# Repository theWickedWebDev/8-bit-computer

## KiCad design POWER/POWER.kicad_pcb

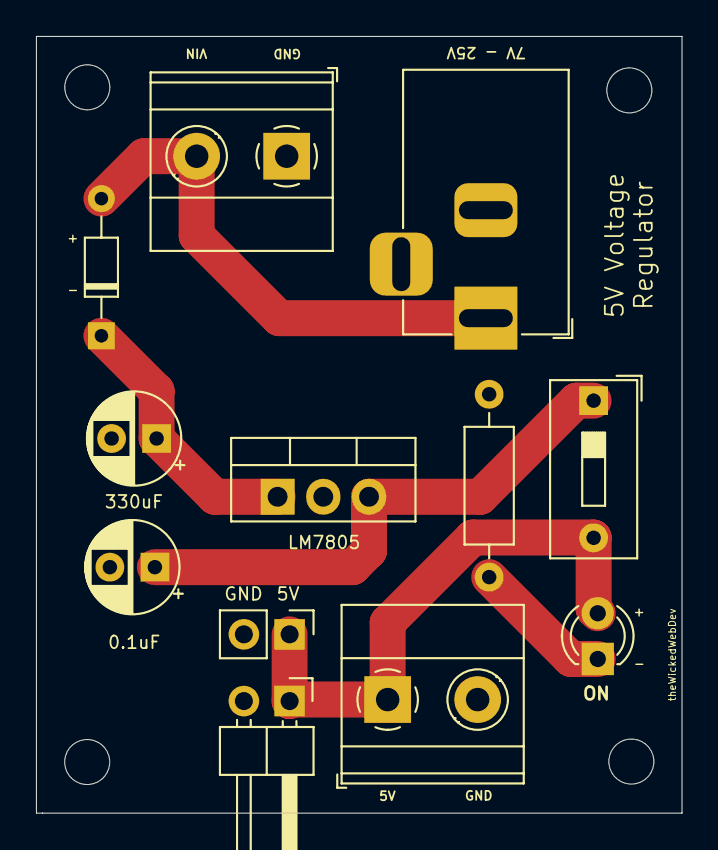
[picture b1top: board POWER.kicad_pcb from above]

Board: 2 copper layers, 35.9 x 43.1 mm, 12 parts (0 on the bottom side), 6 nets.

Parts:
C1, C2: CP1; CP_Radial_D5.0mm_P2.50mm
D1: D_Schottky; D_DO-34_SOD68_P7.62mm_Horizontal
D2: LED; LED_D3.0mm
J1, J4: Screw_Terminal_01x02; TerminalBlock_Phoenix_MKDS-1,5-2_1x02_P5.00mm_Horizontal
J2: Conn_01x02; PinHeader_1x02_P2.54mm_Horizontal
J3: Conn_01x02; PinHeader_1x02_P2.54mm_Vertical
J5: Barrel_Jack_MountingPin; BarrelJack_Horizontal
R1: R_Small_US; R_Axial_DIN0207_L6.3mm_D2.5mm_P10.16mm_Horizontal
SW1: SW_SPST; SW_DIP_SPSTx01_Slide_9.78x4.72mm_W7.62mm_P2.54mm
U1: LM7805_TO220; TO-220-3_Vertical

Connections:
GND: C1.2, C2.2, J1.1, J2.2, J3.2, J4.2, J5.2, R1.2, U1.2
unnamed: C1.1, D1.1, U1.1
unnamed: C2.1, SW1.1, U1.3
unnamed: D1.2, J1.2, J5.1
unnamed: D2.1, R1.1
VCC: D2.2, J2.1, J3.1, J4.1, SW1.2

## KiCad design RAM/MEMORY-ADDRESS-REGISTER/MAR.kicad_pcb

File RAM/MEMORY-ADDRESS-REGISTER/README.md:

# Memory Address Register

TODO: Description coming soon...

<br/>

## QA

<br/>

## PCB

<br/>

<br/>

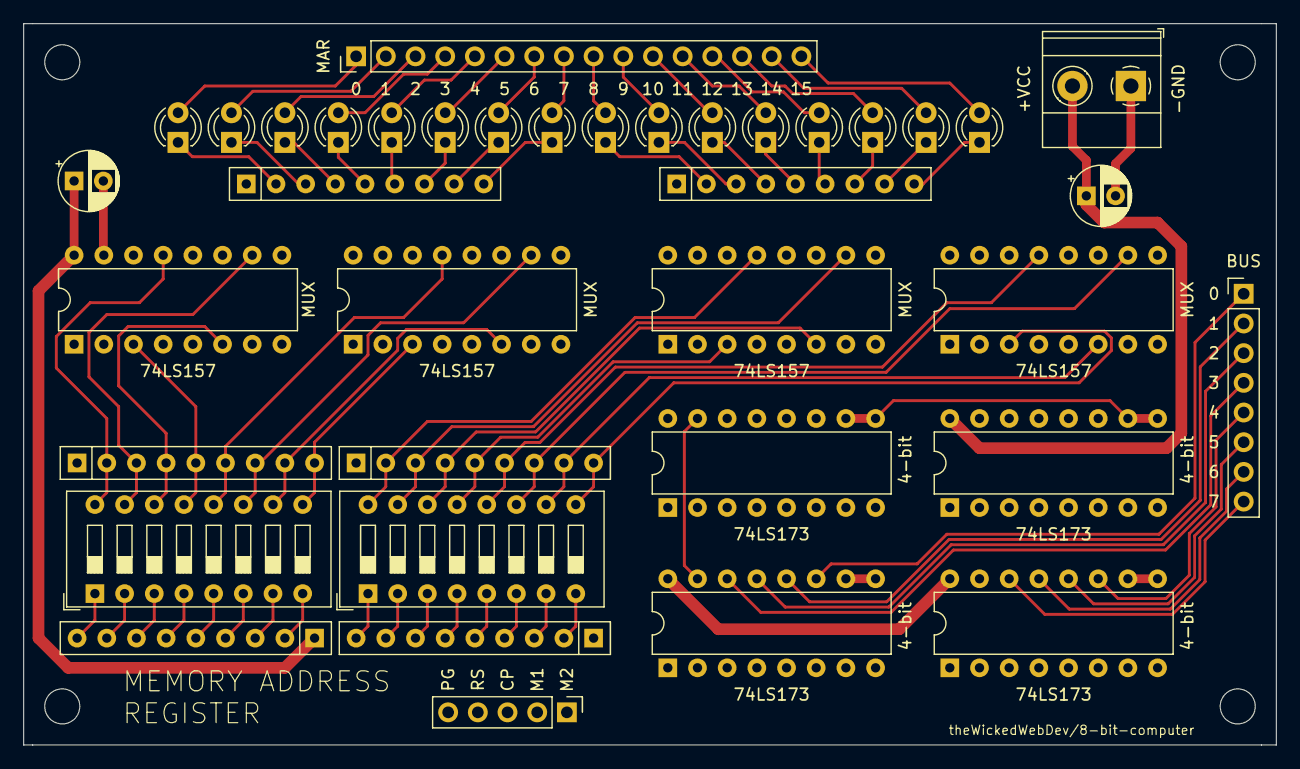
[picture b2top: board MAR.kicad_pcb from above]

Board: 4 copper layers, 107.2 x 61.7 mm, 38 parts (0 on the bottom side), 95 nets.

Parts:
C2, C3: CP1_Small; CP_Radial_D5.0mm_P2.50mm
D1, D2, D3, D4, D5, D6, D7, D8, D9, D10, D11, D12, D13, D14, D15, D16: LED; LED_D3.0mm
J1: Conn_01x08; PinHeader_1x16_P2.54mm_Vertical
J2: Conn_01x08; PinHeader_1x08_P2.54mm_Vertical
J3: Screw_Terminal_01x02; TerminalBlock_Phoenix_MKDS-1,5-2_1x02_P5.00mm_Horizontal
J4: Conn_01x05; PinHeader_1x05_P2.54mm_Vertical
RN1, RN2, RN4, RN5, RN6, RN7: R_Network08_US; R_Array_SIP9
SW1, SW2: SW_DIP_x08; SW_DIP_SPSTx08_Slide_9.78x22.5mm_W7.62mm_P2.54mm
U1, U4, U5, U8: 74LS157; DIP-16_W7.62mm
U2, U3, U6, U7: 74LS173; DIP-16_W7.62mm

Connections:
/CLOCK: J4.3, U2.7, U3.7, U6.7, U7.7
/MANUAL_MEM_ADR_00: RN6.2, SW2.16, U1.13
/MANUAL_MEM_ADR_01: RN6.3, SW2.15, U1.10
/MANUAL_MEM_ADR_02: RN6.4, SW2.14, U1.6
/MANUAL_MEM_ADR_03: RN6.5, SW2.13, U1.3
/MANUAL_MEM_ADR_04: RN6.6, SW2.12, U4.13
/MANUAL_MEM_ADR_05: RN6.7, SW2.11, U4.10
/MANUAL_MEM_ADR_06: RN6.8, SW2.10, U4.6
/MANUAL_MEM_ADR_07: RN6.9, SW2.9, U4.3
/MANUAL_MEM_ADR_08: RN4.2, SW1.16, U5.13
/MANUAL_MEM_ADR_09: RN4.3, SW1.15, U5.10
/MANUAL_MEM_ADR_10: RN4.4, SW1.14, U5.6
/MANUAL_MEM_ADR_11: RN4.5, SW1.13, U5.3
/MANUAL_MEM_ADR_12: RN4.6, SW1.12, U8.13
/MANUAL_MEM_ADR_13: RN4.7, SW1.11, U8.10
/MANUAL_MEM_ADR_14: RN4.8, SW1.10, U8.6
/MANUAL_MEM_ADR_15: RN4.9, SW1.9, U8.3
/MAR1_IN: J4.2, U6.9, U6.10, U7.9, U7.10
/MAR2_IN: J4.1, U2.9, U2.10, U3.9, U3.10
/MAR_00: U1.14, U7.3
/MAR_01: U1.11, U7.4
/MAR_02: U1.5, U7.5
/MAR_03: U1.2, U7.6
/MAR_04: U4.14, U6.3
/MAR_05: U4.11, U6.4
/MAR_06: U4.5, U6.5
/MAR_07: U4.2, U6.6
/MAR_08: U3.3, U5.14
/MAR_09: U3.4, U5.11
/MAR_10: U3.5, U5.5
/MAR_11: U3.6, U5.2
/MAR_12: U2.3, U8.14
/MAR_13: U2.4, U8.11
/MAR_14: U2.5, U8.5
/MAR_15: U2.6, U8.2
/MAR_RESET: J4.4, U2.15, U3.15, U6.15, U7.15
/MEM_ADR_00: D16.2, J1.1, U1.12
/MEM_ADR_01: D15.2, J1.2, U1.9
/MEM_ADR_02: D14.2, J1.3, U1.7
/MEM_ADR_03: D13.2, J1.4, U1.4
/MEM_ADR_04: D12.2, J1.5, U4.12
/MEM_ADR_05: D11.2, J1.6, U4.9
/MEM_ADR_06: D10.2, J1.7, U4.7
/MEM_ADR_07: D9.2, J1.8, U4.4
/MEM_ADR_08: D8.2, J1.9, U5.12
/MEM_ADR_09: D7.2, J1.10, U5.9
/MEM_ADR_10: D6.2, J1.11, U5.7
/MEM_ADR_11: D5.2, J1.12, U5.4
/MEM_ADR_12: D4.2, J1.13, U8.12
/MEM_ADR_13: D3.2, J1.14, U8.9
/MEM_ADR_14: D2.2, J1.15, U8.7
/MEM_ADR_15: D1.2, J1.16, U8.4
/PROGRAM_MODE: J4.5, U1.1, U4.1, U5.1, U8.1
GND: C2.2, C3.2, J3.1, RN1.1, RN2.1, RN4.1, RN6.1, U1.8, U1.15, U2.1, U2.2, U2.8, U3.1, U3.2, U3.8, U4.8, U4.15, U5.8, U5.15, U6.1, U6.2, U6.8, U7.1, U7.2, U7.8, U8.8, U8.15
unnamed: D1.1, RN1.9
unnamed: D2.1, RN1.8
unnamed: D3.1, RN1.7
unnamed: D4.1, RN1.6
unnamed: D5.1, RN1.5
unnamed: D6.1, RN1.4
unnamed: D7.1, RN1.3
unnamed: D8.1, RN1.2
unnamed: D9.1, RN2.9
unnamed: D10.1, RN2.8
unnamed: D11.1, RN2.7
unnamed: D12.1, RN2.6
unnamed: D13.1, RN2.5
unnamed: D14.1, RN2.4
unnamed: D15.1, RN2.3
unnamed: D16.1, RN2.2
unnamed: J2.1, U2.11, U6.11
unnamed: J2.2, U2.12, U6.12
unnamed: J2.3, U2.13, U6.13
unnamed: J2.4, U2.14, U6.14
unnamed: J2.5, U3.11, U7.11
unnamed: J2.6, U3.12, U7.12
unnamed: J2.7, U3.13, U7.13
unnamed: J2.8, U3.14, U7.14
unnamed: RN5.2, SW1.8
unnamed: RN5.3, SW1.7
unnamed: RN5.4, SW1.6
unnamed: RN5.5, SW1.5
unnamed: RN5.6, SW1.4
unnamed: RN5.7, SW1.3
unnamed: RN5.8, SW1.2
unnamed: RN5.9, SW1.1
unnamed: RN7.2, SW2.8
unnamed: RN7.3, SW2.7
unnamed: RN7.4, SW2.6
unnamed: RN7.5, SW2.5
unnamed: RN7.6, SW2.4
unnamed: RN7.7, SW2.3
unnamed: RN7.8, SW2.2
unnamed: RN7.9, SW2.1
VCC: C2.1, C3.1, J3.2, RN5.1, RN7.1, U1.16, U2.16, U3.16, U4.16, U5.16, U6.16, U7.16, U8.16

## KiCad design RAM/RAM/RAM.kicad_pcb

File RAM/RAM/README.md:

# RAM Modules

TODO: Description coming soon...

<br/>

## QA

<br/>

## PCB

<br/>

<br/>

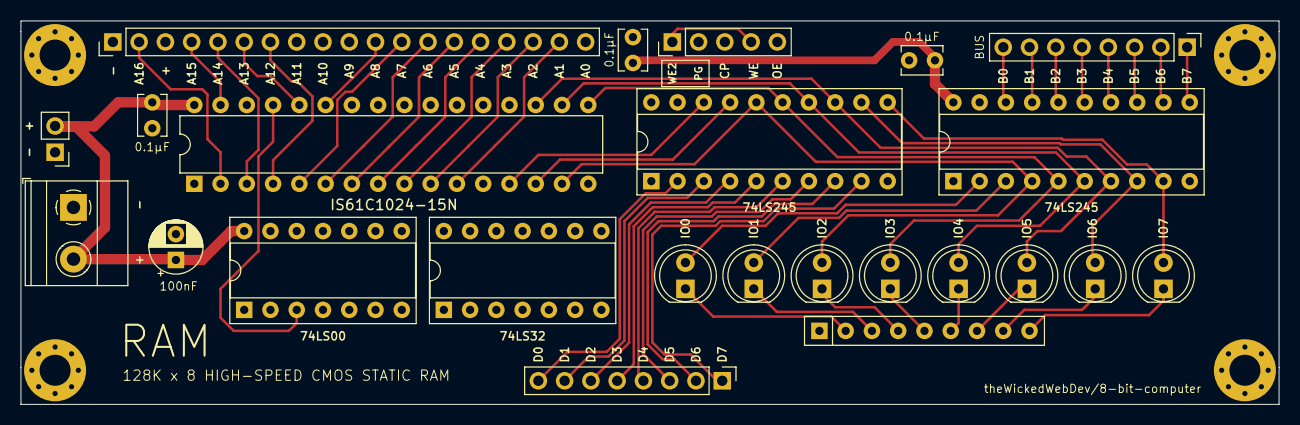
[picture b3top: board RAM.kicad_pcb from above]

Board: 4 copper layers, 121.7 x 37.1 mm, 24 parts (0 on the bottom side), 57 nets.

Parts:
C1: CP1_Small; CP_Radial_D5.0mm_P2.50mm
C2, C3, C4: C_Small; C_Disc_D3.8mm_W2.6mm_P2.50mm
D1, D2, D3, D4, D5, D6, D7, D8: LED; LED_D5.0mm
J1: Conn_01x19; PinHeader_1x19_P2.54mm_Vertical
J2: Conn_01x05; PinHeader_1x05_P2.54mm_Vertical
J3: Conn_01x02; PinHeader_1x02_P2.54mm_Vertical
J4: Screw_Terminal_01x02; TerminalBlock_Phoenix_MKDS-1,5-2_1x02_P5.00mm_Horizontal
J6, J7: Conn_01x08; PinHeader_1x08_P2.54mm_Vertical
RN1: R_Network08_US; R_Array_SIP9
U1: IS61C1024-15N; DIP-32_W7.62mm
U2, U3: 74LS245; DIP-20_W7.62mm_Socket
U4: 74LS00; DIP-14_W7.62mm_Socket
U6: 74LS32; DIP-14_W7.62mm_Socket

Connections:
/IO0: D8.2, U1.13, U2.2, U3.18
/IO1: D7.2, U1.14, U2.3, U3.17
/IO2: D6.2, U1.15, U2.4, U3.16
/IO3: D5.2, U1.17, U2.5, U3.15
/IO4: D4.2, U1.18, U2.6, U3.14
/IO5: D3.2, U1.19, U2.7, U3.13
/IO6: D2.2, U1.20, U2.8, U3.12
/IO7: D1.2, U1.21, U2.9, U3.11
A0: J1.19, U1.12
A1: J1.18, U1.11
A2: J1.17, U1.10
A3: J1.16, U1.9
A4: J1.15, U1.8
A5: J1.14, U1.7
A6: J1.13, U1.6
A7: J1.12, U1.5
A8: J1.11, U1.27
A9: J1.10, U1.26
A10: J1.9, U1.23
A11: J1.8, U1.25
A12: J1.7, U1.4
A13: J1.6, U1.28
A14: J1.5, U1.3
A15: J1.4, U1.31
A16: J1.2, U1.2
BUS0: J6.8, U2.18
BUS1: J6.7, U2.17
BUS2: J6.6, U2.16
BUS3: J6.5, U2.15
BUS4: J6.4, U2.14
BUS5: J6.3, U2.13
BUS6: J6.2, U2.12
BUS7: J6.1, U2.11
CLOCK: J2.3, U6.2
D0: J7.8, U3.2
D1: J7.7, U3.3
D2: J7.6, U3.4
D3: J7.5, U3.5
D4: J7.4, U3.6
D5: J7.3, U3.7
D6: J7.2, U3.8
D7: J7.1, U3.9
GND: C1.2, C2.2, C3.2, C4.2, J1.1, J3.1, J4.1, RN1.1, U1.16, U1.22, U1.24, U2.10, U3.10, U4.7, U6.7
unnamed: D1.1, RN1.9
unnamed: D2.1, RN1.8
unnamed: D3.1, RN1.7
unnamed: D4.1, RN1.6
unnamed: D5.1, RN1.5
unnamed: D6.1, RN1.4
unnamed: D7.1, RN1.3
unnamed: D8.1, RN1.2
unnamed: U1.29, U3.19, U4.3
unnamed: U4.1, U6.3
OUTPUT_ENABLE: J2.5, U2.19
PROGRAM_MODE: J2.2, U6.1
VCC: C1.1, C2.1, C3.1, C4.1, J1.3, J3.2, J4.2, U1.30, U1.32, U2.1, U2.20, U3.1, U3.20, U4.14, U6.14
WRITE_ENABLE: J2.1, J2.4, U4.2

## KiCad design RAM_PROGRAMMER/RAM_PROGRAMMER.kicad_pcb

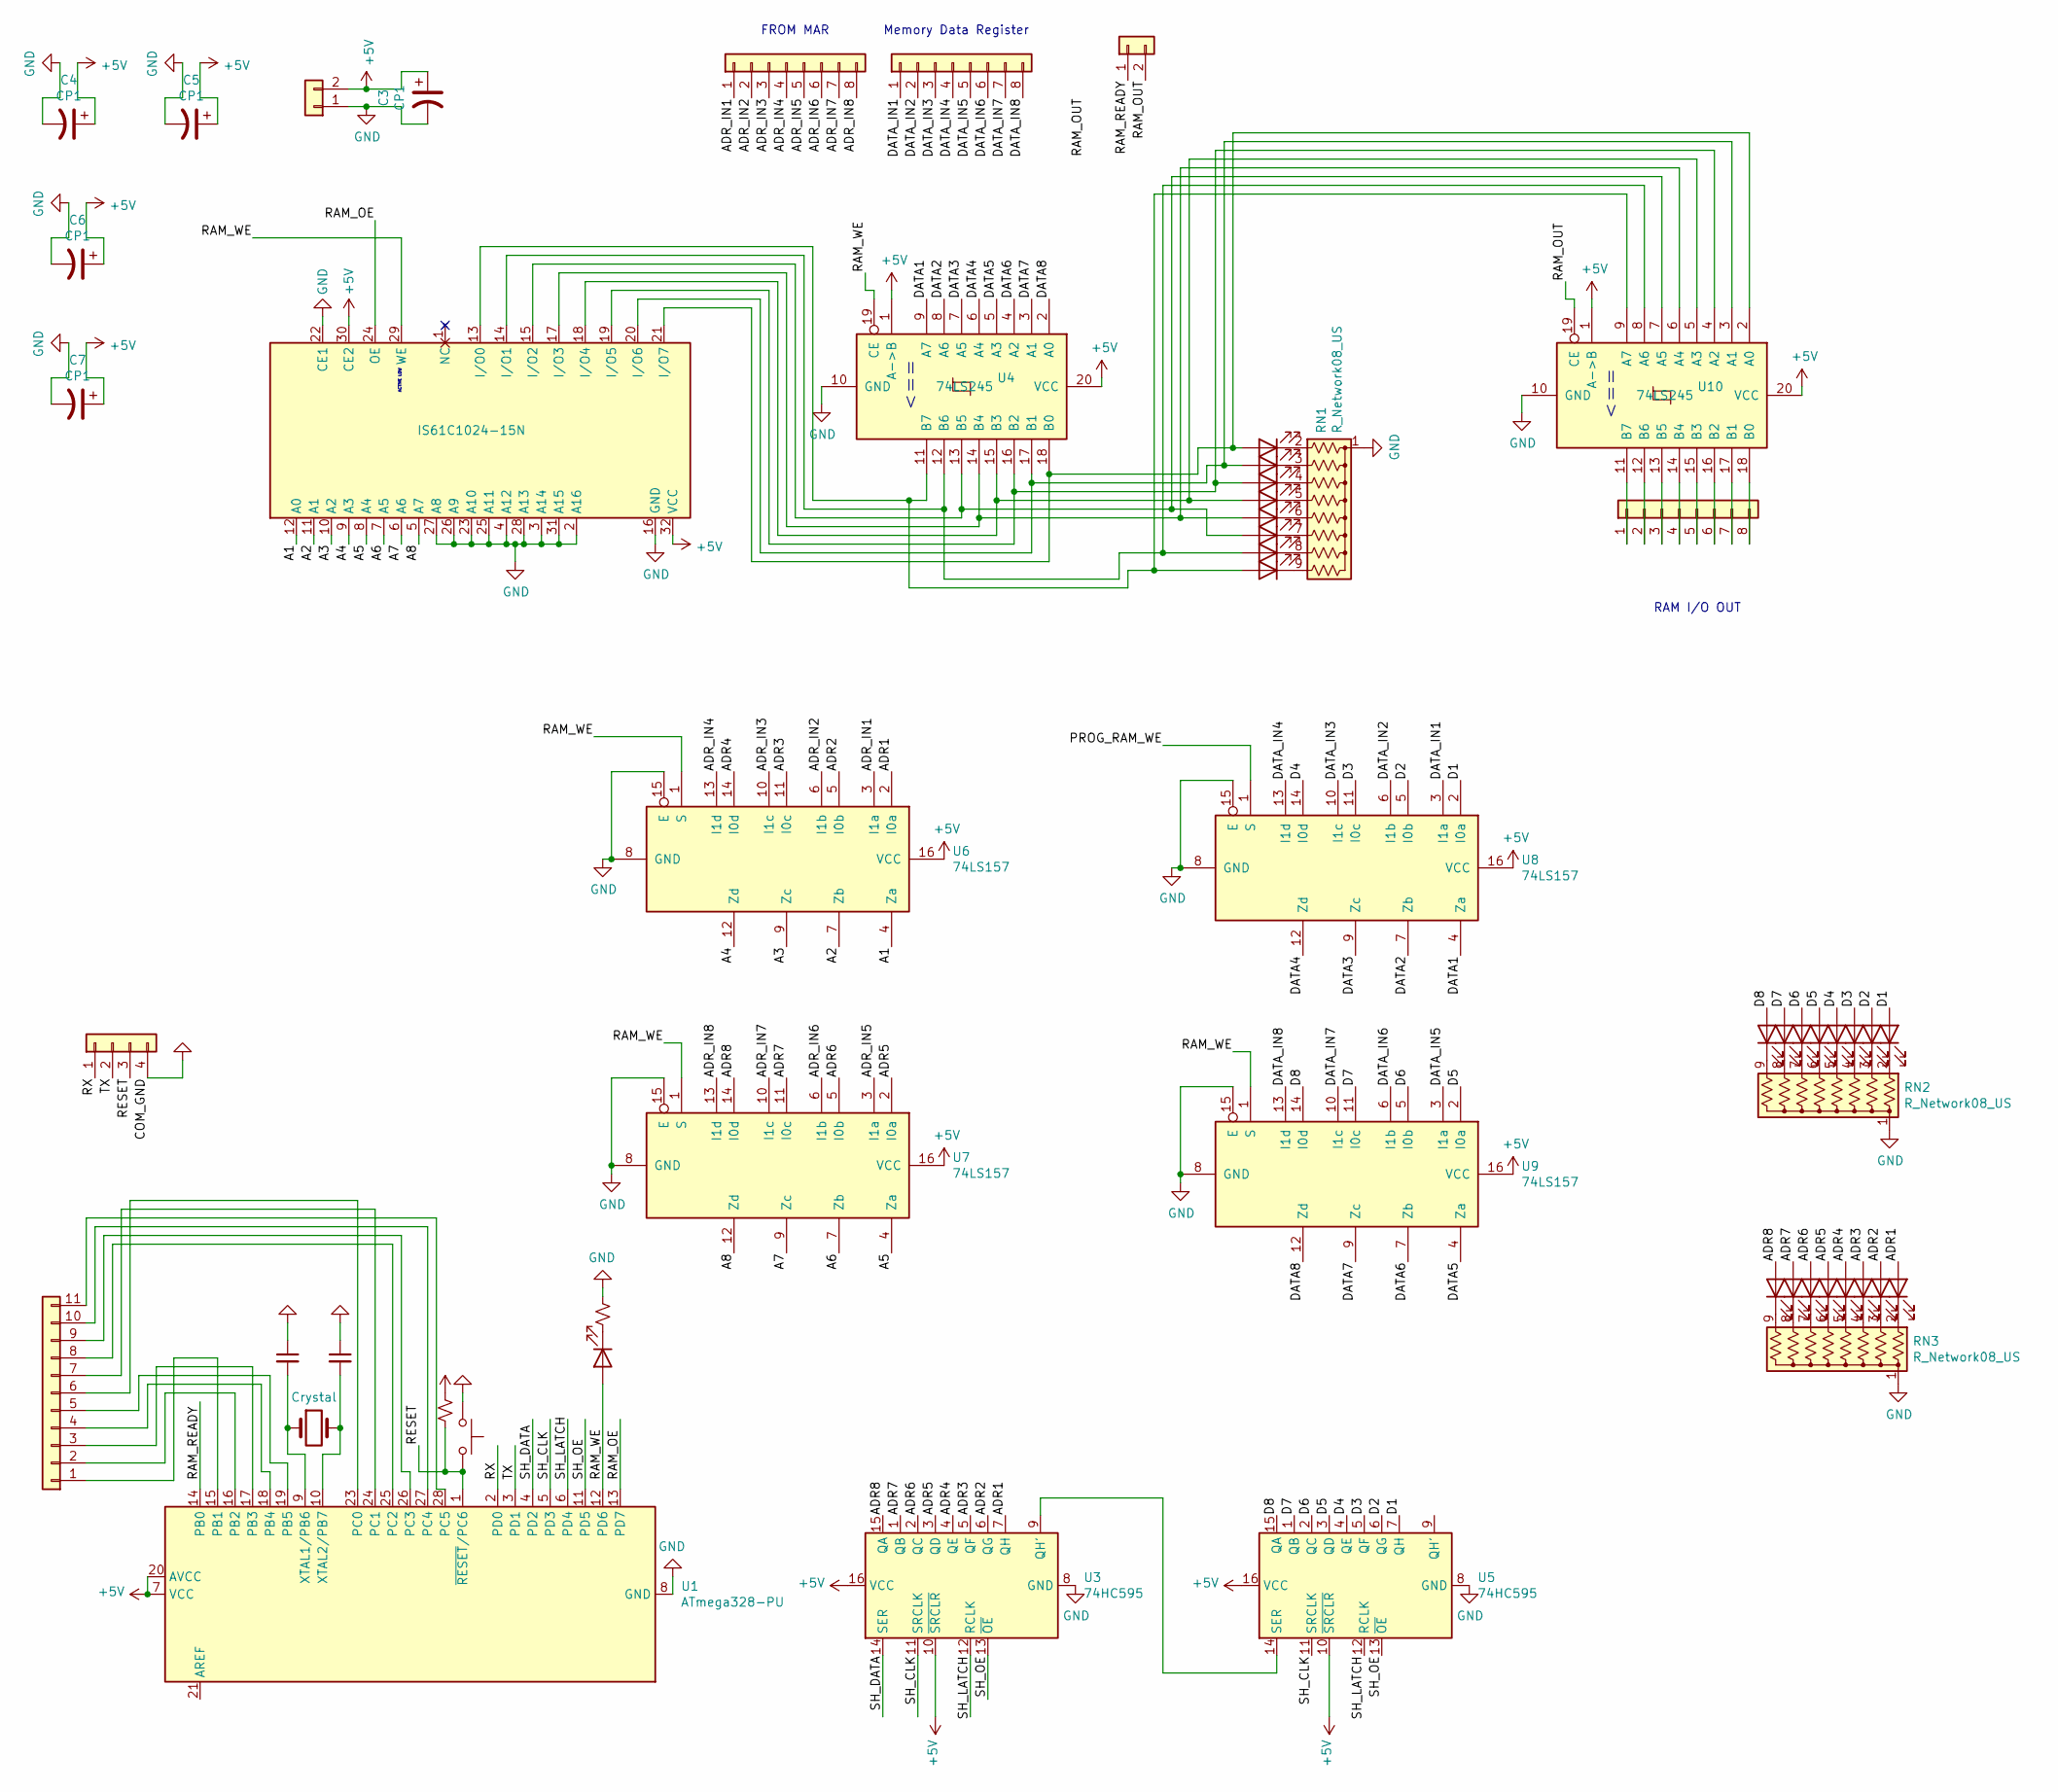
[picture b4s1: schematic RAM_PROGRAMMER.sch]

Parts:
C1, C2: C_Small; C_Disc_D3.8mm_W2.6mm_P2.50mm
C3, C4, C5, C6, C7: CP1; C_Radial_D4.0mm_H5.0mm_P1.50mm
D1, D2, D3, D4, D5, D6, D7, D8, D9, D10, D11, D12, D13, D14, D15, D16, D17, D18, D19, D20, D21, D22, D23, D24, D25: LED; LED_D3.0mm
J1, J5: Conn_01x02; PinHeader_1x02_P2.54mm_Vertical
J2, J3, J4: Conn_01x08; PinHeader_1x08_P2.54mm_Vertical
J6: Conn_01x04; PinHeader_1x04_P2.54mm_Vertical
J7: Conn_01x11; PinHeader_1x11_P2.54mm_Vertical
R1: R_Small_US; R_Axial_DIN0207_L6.3mm_D2.5mm_P7.62mm_Horizontal
R2: R_Small_US; R_Axial_DIN0204_L3.6mm_D1.6mm_P7.62mm_Horizontal
RN1, RN2, RN3: R_Network08_US; R_Array_SIP9
SW1: SW_Push; SW_PUSH_6mm
U1: ATmega328-PU; DIP-28_W7.62mm
U2: IS61C1024-15N; DIP-32_W7.62mm
U3, U5: 74HC595; DIP-16_W7.62mm
U4, U10: 74LS245; DIP-20_W7.62mm
U6, U7, U8, U9: 74LS157; DIP-16_W7.62mm
Y1: Crystal; Resonator-2Pin_W7.0mm_H2.5mm

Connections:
+5V: C3.1, C4.1, C5.1, C6.1, C7.1, J1.2, R1.1, U1.7 (VCC), U1.20 (AVCC), U2.30 (CE2), U2.32 (VCC), U3.10 (~SRCLR), U3.16 (VCC), U4.1 (A->B), U4.20 (VCC), U5.10 (~SRCLR), U5.16 (VCC), U6.16 (VCC), U7.16 (VCC), U8.16 (VCC), U9.16 (VCC), U10.1 (A->B), U10.20 (VCC)
/A1: U2.12 (A0), U6.4 (Za)
/A2: U2.11 (A1), U6.7 (Zb)
/A3: U2.10 (A2), U6.9 (Zc)
/A4: U2.9 (A3), U6.12 (Zd)
/A5: U2.8 (A4), U7.4 (Za)
/A6: U2.7 (A5), U7.7 (Zb)
/A7: U2.6 (A6), U7.9 (Zc)
/A8: U2.5 (A7), U7.12 (Zd)
/ADR1: D24.2 (A), U3.7 (QH), U6.2 (I0a)
/ADR2: D22.2 (A), U3.6 (QG), U6.5 (I0b)
/ADR3: D20.2 (A), U3.5 (QF), U6.11 (I0c)
/ADR4: D18.2 (A), U3.4 (QE), U6.14 (I0d)
/ADR5: D16.2 (A), U3.3 (QD), U7.2 (I0a)
/ADR6: D14.2 (A), U3.2 (QC), U7.5 (I0b)
/ADR7: D12.2 (A), U3.1 (QB), U7.11 (I0c)
/ADR8: D10.2 (A), U3.15 (QA), U7.14 (I0d)
/ADR_IN1: J2.1, U6.3 (I1a)
/ADR_IN2: J2.2, U6.6 (I1b)
/ADR_IN3: J2.3, U6.10 (I1c)
/ADR_IN4: J2.4, U6.13 (I1d)
/ADR_IN5: J2.5, U7.3 (I1a)
/ADR_IN6: J2.6, U7.6 (I1b)
/ADR_IN7: J2.7, U7.10 (I1c)
/ADR_IN8: J2.8, U7.13 (I1d)
/D1: D23.2 (A), U5.7 (QH), U8.2 (I0a)
/D2: D21.2 (A), U5.6 (QG), U8.5 (I0b)
/D3: D19.2 (A), U5.5 (QF), U8.11 (I0c)
/D4: D17.2 (A), U5.4 (QE), U8.14 (I0d)
/D5: D15.2 (A), U5.3 (QD), U9.2 (I0a)
/D6: D13.2 (A), U5.2 (QC), U9.5 (I0b)
/D7: D11.2 (A), U5.1 (QB), U9.11 (I0c)
/D8: D9.2 (A), U5.15 (QA), U9.14 (I0d)
/DATA1: U4.9 (A7), U8.4 (Za)
/DATA2: U4.8 (A6), U8.7 (Zb)
/DATA3: U4.7 (A5), U8.9 (Zc)
/DATA4: U4.6 (A4), U8.12 (Zd)
/DATA5: U4.5 (A3), U9.4 (Za)
/DATA6: U4.4 (A2), U9.7 (Zb)
/DATA7: U4.3 (A1), U9.9 (Zc)
/DATA8: U4.2 (A0), U9.12 (Zd)
/DATA_IN1: J3.1, U8.3 (I1a)
/DATA_IN2: J3.2, U8.6 (I1b)
/DATA_IN3: J3.3, U8.10 (I1c)
/DATA_IN4: J3.4, U8.13 (I1d)
/DATA_IN5: J3.5, U9.3 (I1a)
/DATA_IN6: J3.6, U9.6 (I1b)
/DATA_IN7: J3.7, U9.10 (I1c)
/DATA_IN8: J3.8, U9.13 (I1d)
/PROG_RAM_WE: U8.1 (S)
/RAM_OE: U1.13 (PD7), U2.24 (OE)
/RAM_OUT: J5.2, U10.19 (CE)
/RAM_READY: J5.1, U1.14 (PB0)
/RAM_WE: D25.2 (A), U1.12 (PD6), U2.29 (WE), U4.19 (CE), U6.1 (S), U7.1 (S), U9.1 (S)
/RESET: J6.3, R1.2, SW1.2, U1.1 (~RESET~/PC6)
/RX: J6.1, U1.2 (PD0)
/SH_CLK: U1.5 (PD3), U3.11 (SRCLK), U5.11 (SRCLK)
/SH_DATA: U1.4 (PD2), U3.14 (SER)
/SH_LATCH: U1.6 (PD4), U3.12 (RCLK), U5.12 (RCLK)
/SH_OE: U1.11 (PD5), U3.13 (~OE), U5.13 (~OE)
/TX: J6.2, U1.3 (PD1)
GND: C1.1, C2.1, C3.2, C4.2, C5.2, C6.2, C7.2, J1.1, J6.4, R2.2, RN1.1 (common), RN2.1 (common), RN3.1 (common), SW1.1, U1.8 (GND), U1.22 (GND), U2.2 (A16), U2.3 (A14), U2.4 (A12), U2.16 (GND), U2.22 (CE1), U2.23 (A10), U2.25 (A11), U2.26 (A9), U2.27 (A8), U2.28 (A13), U2.31 (A15), U3.8 (GND), U4.10 (GND), U5.8 (GND), U6.8 (GND), U6.15 (E), U7.8 (GND), U7.15 (E), U8.8 (GND), U8.15 (E), U9.8 (GND), U9.15 (E), U10.10 (GND)
unnamed: C1.2, U1.9 (XTAL1/PB6), Y1.1
unnamed: C2.2, U1.10 (XTAL2/PB7), Y1.2
unnamed: D1.1 (K), RN1.2 (R1)
unnamed: D1.2 (A), U2.21 (I/O7), U4.18 (B0), U10.2 (A0)
unnamed: D2.1 (K), RN1.3 (R2)
unnamed: D2.2 (A), U2.20 (I/O6), U4.17 (B1), U10.3 (A1)
unnamed: D3.1 (K), RN1.4 (R3)
unnamed: D3.2 (A), U2.19 (I/O5), U4.16 (B2), U10.4 (A2)
unnamed: D4.1 (K), RN1.5 (R4)
unnamed: D4.2 (A), U2.18 (I/O4), U4.15 (B3), U10.5 (A3)
unnamed: D5.1 (K), RN1.6 (R5)
unnamed: D5.2 (A), U2.17 (I/O3), U4.14 (B4), U10.6 (A4)
unnamed: D6.1 (K), RN1.7 (R6)
unnamed: D6.2 (A), U2.15 (I/O2), U4.13 (B5), U10.7 (A5)
unnamed: D7.1 (K), RN1.8 (R7)
unnamed: D7.2 (A), U2.14 (I/O1), U4.12 (B6), U10.8 (A6)
unnamed: D8.1 (K), RN1.9 (R8)
unnamed: D8.2 (A), U2.13 (I/O0), U4.11 (B7), U10.9 (A7)
unnamed: D9.1 (K), RN2.9 (R8)
unnamed: D10.1 (K), RN3.9 (R8)
unnamed: D11.1 (K), RN2.8 (R7)
unnamed: D12.1 (K), RN3.8 (R7)
unnamed: D13.1 (K), RN2.7 (R6)
unnamed: D14.1 (K), RN3.7 (R6)
unnamed: D15.1 (K), RN2.6 (R5)
unnamed: D16.1 (K), RN3.6 (R5)
unnamed: D17.1 (K), RN2.5 (R4)
unnamed: D18.1 (K), RN3.5 (R4)
unnamed: D19.1 (K), RN2.4 (R3)
unnamed: D20.1 (K), RN3.4 (R3)
unnamed: D21.1 (K), RN2.3 (R2)
unnamed: D22.1 (K), RN3.3 (R2)
unnamed: D23.1 (K), RN2.2 (R1)
unnamed: D24.1 (K), RN3.2 (R1)
unnamed: D25.1 (K), R2.1
unnamed: J4.1, U10.11 (B7)
unnamed: J4.2, U10.12 (B6)
unnamed: J4.3, U10.13 (B5)
unnamed: J4.4, U10.14 (B4)
unnamed: J4.5, U10.15 (B3)
unnamed: J4.6, U10.16 (B2)
unnamed: J4.7, U10.17 (B1)
unnamed: J4.8, U10.18 (B0)
unnamed: J7.1, U1.15 (PB1)
unnamed: J7.2, U1.16 (PB2)
unnamed: J7.3, U1.17 (PB3)
unnamed: J7.4, U1.18 (PB4)
unnamed: J7.5, U1.19 (PB5)
unnamed: J7.6, U1.23 (PC0)
unnamed: J7.7, U1.24 (PC1)
unnamed: J7.8, U1.25 (PC2)
unnamed: J7.9, U1.26 (PC3)
unnamed: J7.10, U1.27 (PC4)
unnamed: J7.11, U1.28 (PC5)
unnamed: U3.9 (QH'), U5.14 (SER)

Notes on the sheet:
<==
ACTIVE LOW
FROM MAR
Memory Data Register
RAM I/O OUT

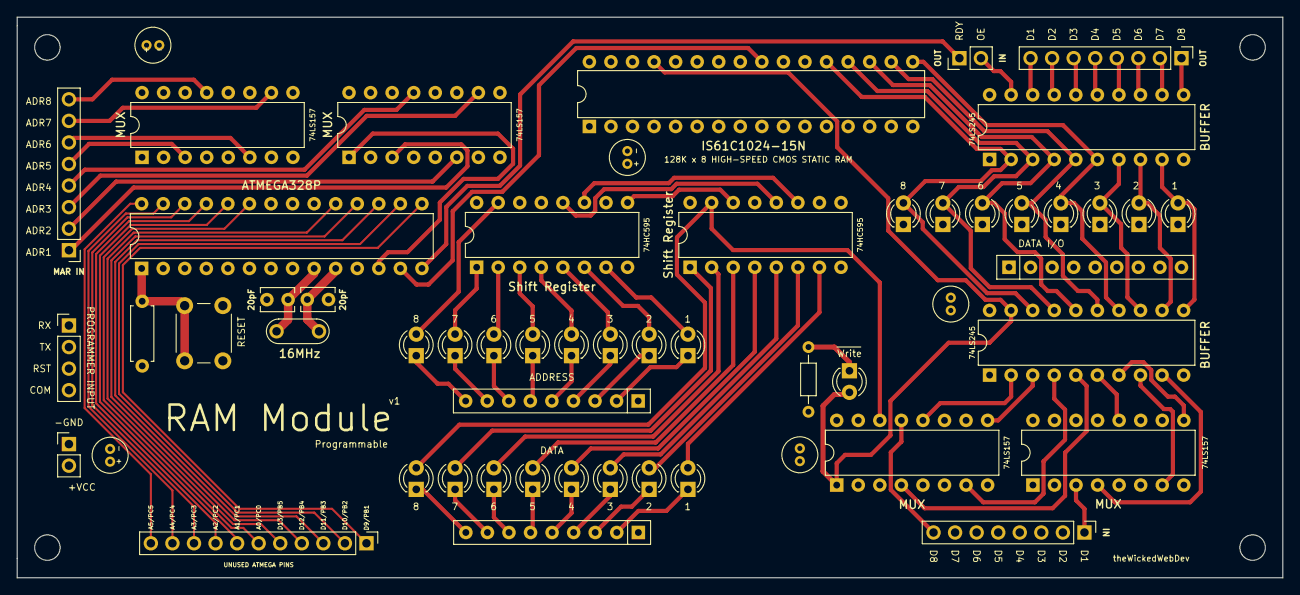
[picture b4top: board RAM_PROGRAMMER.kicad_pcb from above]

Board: 4 copper layers, 149.1 x 66.0 mm, 56 parts (0 on the bottom side), 116 nets.

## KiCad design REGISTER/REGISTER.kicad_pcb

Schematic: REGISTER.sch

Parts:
C1, C2, C3, C4: CP1; C_Radial_D5.0mm_H7.0mm_P2.00mm
D1, D2, D3, D4, D5, D6, D7, D8, D9, D10, D11, D12, D13, D14, D15, D16: LED; LED_D5.0mm
J1, J2, J5, J7, J8: Conn_01x08; PinHeader_1x08_P2.54mm_Vertical
J3: Conn_01x02; PinHeader_1x02_P2.54mm_Vertical
J6: Conn_01x07; PinHeader_1x07_P2.54mm_Vertical
RN1, RN2: R_Network08; R_Array_SIP9
U1, U4: 74LS245; DIP-20_W7.62mm
U2, U3, U5, U6: 74LS173; DIP-16_W7.62mm

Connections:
/A1: D8.2 (A), J7.1, J8.1, U1.9 (A7), U3.6 (Q3)
/A2: D7.2 (A), J7.2, J8.2, U1.8 (A6), U3.5 (Q2)
/A3: D6.2 (A), J7.3, J8.3, U1.7 (A5), U3.4 (Q1)
/A4: D5.2 (A), J7.4, J8.4, U1.6 (A4), U3.3 (Q0)
/A5: D4.2 (A), J7.5, J8.5, U1.5 (A3), U2.6 (Q3)
/A6: D3.2 (A), J7.6, J8.6, U1.4 (A2), U2.5 (Q2)
/A7: D2.2 (A), J7.7, J8.7, U1.3 (A1), U2.4 (Q1)
/A8: D1.2 (A), J7.8, J8.8, U1.2 (A0), U2.3 (Q0)
/AI: J6.5, U2.9 (E1), U2.10 (E2), U3.9 (E1), U3.10 (E2)
/AO: J6.4, U1.19 (CE)
/B1: D16.2 (A), J1.1, J2.1, U4.9 (A7), U6.6 (Q3)
/B2: D15.2 (A), J1.2, J2.2, U4.8 (A6), U6.5 (Q2)
/B3: D14.2 (A), J1.3, J2.3, U4.7 (A5), U6.4 (Q1)
/B4: D13.2 (A), J1.4, J2.4, U4.6 (A4), U6.3 (Q0)
/B5: D12.2 (A), J1.5, J2.5, U4.5 (A3), U5.6 (Q3)
/B6: D11.2 (A), J1.6, J2.6, U4.4 (A2), U5.5 (Q2)
/B7: D10.2 (A), J1.7, J2.7, U4.3 (A1), U5.4 (Q1)
/B8: D9.2 (A), J1.8, J2.8, U4.2 (A0), U5.3 (Q0)
/BI: J6.2, U5.9 (E1), U5.10 (E2), U6.9 (E1), U6.10 (E2)
/BO: J6.1, U4.19 (CE)
/CLK: J6.7, U2.7 (Cp), U3.7 (Cp), U5.7 (Cp), U6.7 (Cp)
/I1: J5.8, U1.11 (B7), U3.11 (D3), U4.11 (B7), U6.11 (D3)
/I2: J5.7, U1.12 (B6), U3.12 (D2), U4.12 (B6), U6.12 (D2)
/I3: J5.6, U1.13 (B5), U3.13 (D1), U4.13 (B5), U6.13 (D1)
/I4: J5.5, U1.14 (B4), U3.14 (D0), U4.14 (B4), U6.14 (D0)
/I5: J5.4, U1.15 (B3), U2.11 (D3), U4.15 (B3), U5.11 (D3)
/I6: J5.3, U1.16 (B2), U2.12 (D2), U4.16 (B2), U5.12 (D2)
/I7: J5.2, U1.17 (B1), U2.13 (D1), U4.17 (B1), U5.13 (D1)
/I8: J5.1, U1.18 (B0), U2.14 (D0), U4.18 (B0), U5.14 (D0)
GND: C1.2, C2.2, C3.2, C4.2, J3.2, RN1.1, RN2.1, U1.10 (GND), U2.1 (Oe1), U2.2 (Oe2), U2.8 (GND), U3.1 (Oe1), U3.2 (Oe2), U3.8 (GND), U4.10 (GND), U5.1 (Oe1), U5.2 (Oe2), U5.8 (GND), U6.1 (Oe1), U6.2 (Oe2), U6.8 (GND)
unnamed: D1.1 (K), RN1.9
unnamed: D2.1 (K), RN1.8
unnamed: D3.1 (K), RN1.7
unnamed: D4.1 (K), RN1.6
unnamed: D5.1 (K), RN1.5
unnamed: D6.1 (K), RN1.4
unnamed: D7.1 (K), RN1.3
unnamed: D8.1 (K), RN1.2
unnamed: D9.1 (K), RN2.9
unnamed: D10.1 (K), RN2.8
unnamed: D11.1 (K), RN2.7
unnamed: D12.1 (K), RN2.6
unnamed: D13.1 (K), RN2.5
unnamed: D14.1 (K), RN2.4
unnamed: D15.1 (K), RN2.3
unnamed: D16.1 (K), RN2.2
VCC: C1.1, C2.1, C3.1, C4.1, J3.1, U1.1 (A->B), U1.20 (VCC), U2.16 (VCC), U3.16 (VCC), U4.1 (A->B), U4.20 (VCC), U5.16 (VCC), U6.16 (VCC)

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
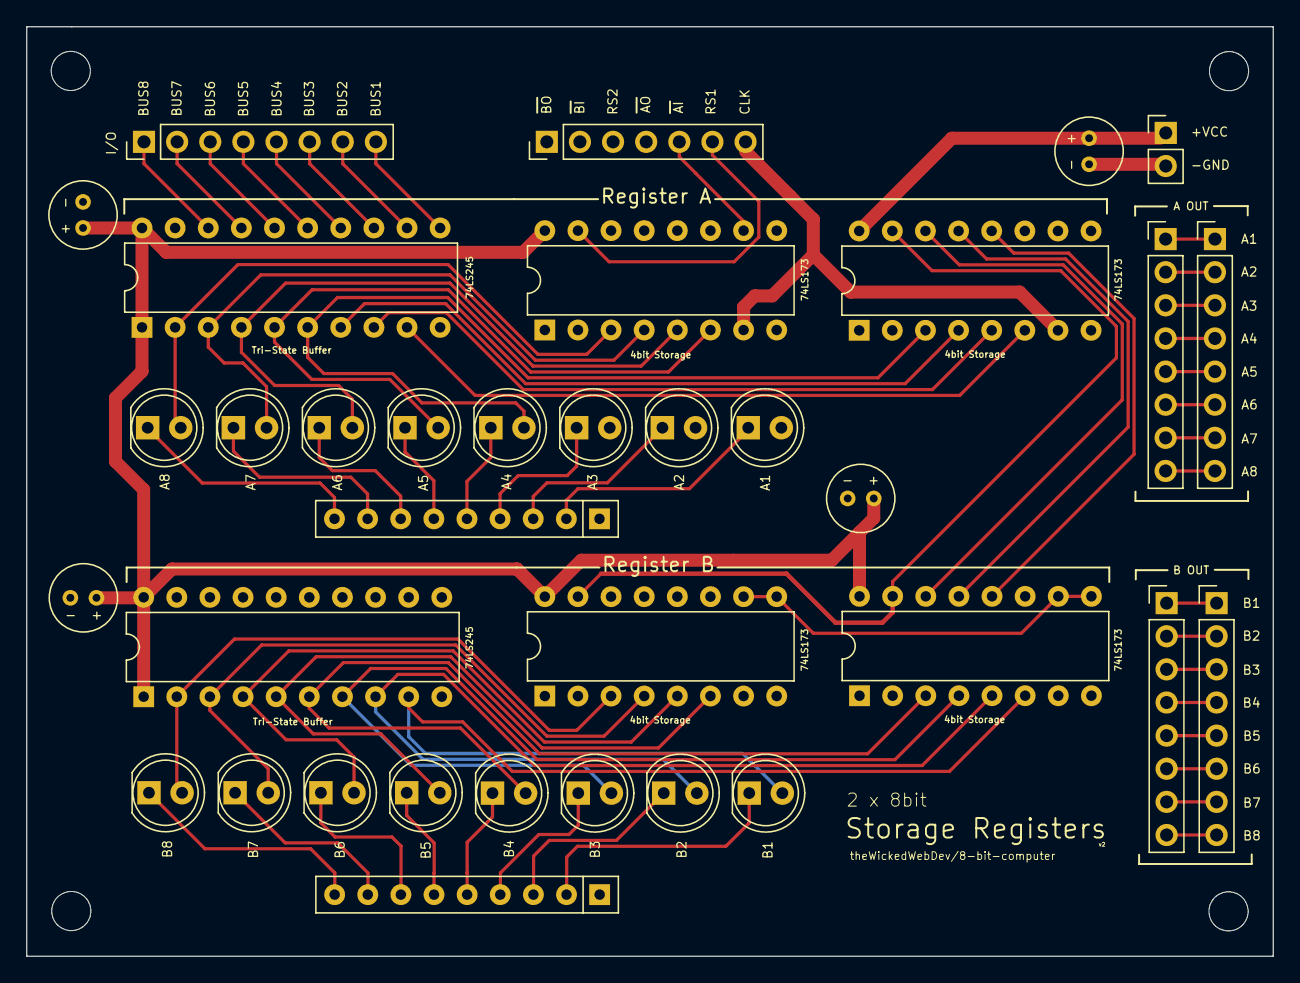
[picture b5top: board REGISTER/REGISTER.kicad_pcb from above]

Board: 4 copper layers, 95.6 x 71.3 mm, 35 parts (0 on the bottom side), 48 nets.

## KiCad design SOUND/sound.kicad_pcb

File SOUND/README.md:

# Sound / Audio Module

TODO: Description coming soon...

<br/>

## Breadboard 8038 IC

Simple function generator test

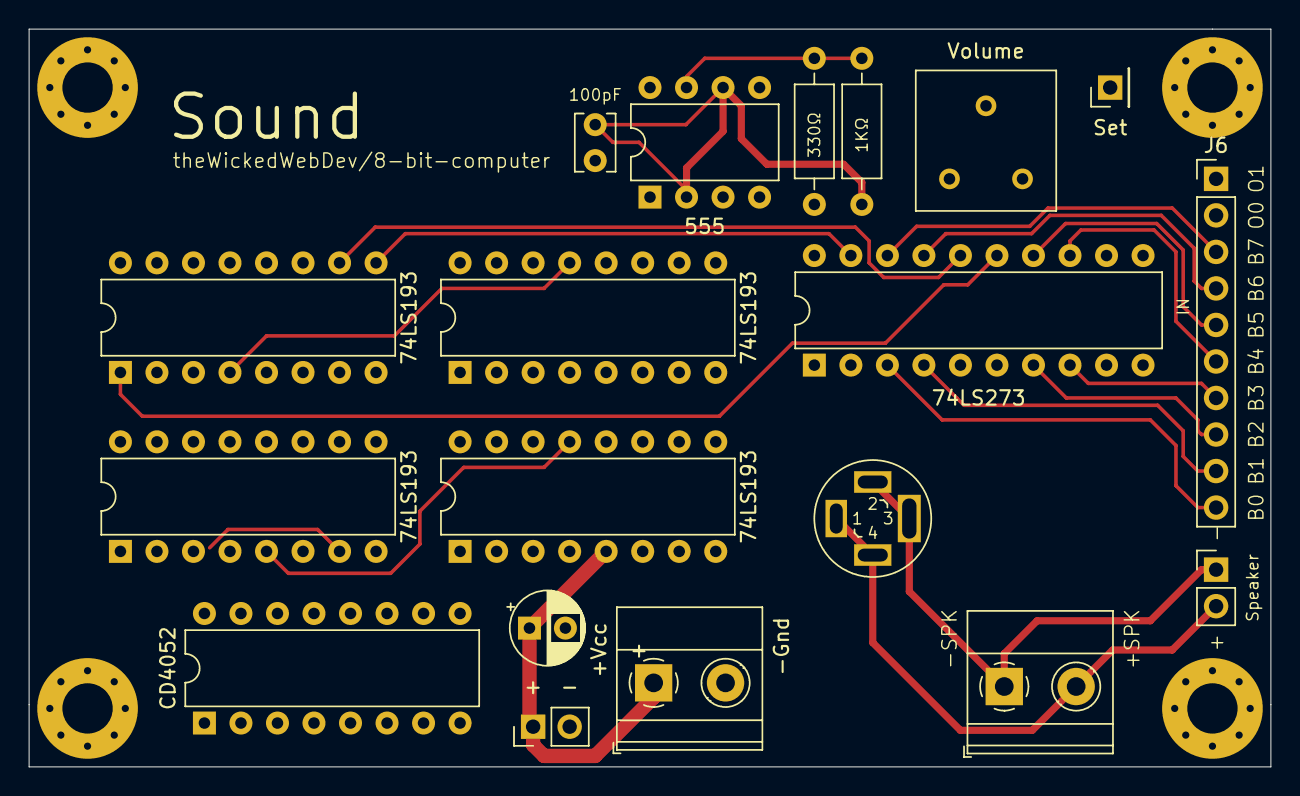
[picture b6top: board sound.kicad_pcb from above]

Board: 4 copper layers, 86.4 x 51.3 mm, 19 parts (0 on the bottom side), 33 nets.

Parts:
C1: C; C_Disc_D3.8mm_W2.6mm_P2.50mm
C3: CP1_Small; CP_Radial_D5.0mm_P2.50mm
J1, J2: Conn_01x02; PinHeader_1x02_P2.54mm_Vertical
J3: Conn_01x01; PinHeader_1x01_P2.54mm_Vertical
J5, J7: Screw_Terminal_01x02; TerminalBlock_Phoenix_MKDS-1,5-2_1x02_P5.00mm_Horizontal
J6: Conn_01x10; PinHeader_1x10_P2.54mm_Vertical
LS1: Speaker; 3.5mm_Audio_Jack_PJ31640M
R1, R2: R_Small_US; R_Axial_DIN0207_L6.3mm_D2.5mm_P10.16mm_Horizontal
RV1: R_POT_TRIM_US; Potentiometer_Bourns_3386F_Vertical
U1, U3, U4, U5: 74LS193; DIP-16_W7.62mm
U2: LM555xN; DIP-8_W7.62mm
U6: 74LS273; DIP-20_W7.62mm
U7: CD4052B; DIP-16_W7.62mm

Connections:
BUS_00: J6.10, U6.3
BUS_01: J6.9, U6.4
BUS_02: J6.8, U6.7
BUS_03: J6.7, U6.8
BUS_04: J6.6, U6.13
BUS_05: J6.5, U6.14
BUS_06: J6.4, U6.17
BUS_07: J6.3, U6.18
GND: C1.1, C3.2, J2.2, J5.2, RV1.3, U1.8, U1.14, U2.1, U3.1, U3.8, U3.9, U3.10, U3.14, U3.15, U4.8, U4.14, U5.8, U5.14, U6.10, U7.6, U7.7, U7.8
LATCH_NOTE: J3.1, U6.11
unnamed: C1.2, R1.1, U2.2, U2.6
unnamed: J1.1, J7.1, LS1.R1, LS1.R2, RV1.2
unnamed: R1.2, R2.2, U2.7
unnamed: U1.2, U7.15
unnamed: U1.3, U7.11
unnamed: U1.5, U3.11, U3.13, U4.11, U5.11
unnamed: U1.6, U7.14
unnamed: U1.7, U7.12
unnamed: U2.3, U5.4
unnamed: U3.4, U4.13
unnamed: U4.1, U6.15
unnamed: U4.4, U5.13
unnamed: U4.9, U6.19
unnamed: U4.10, U6.16
unnamed: U4.15, U6.12
unnamed: U5.1, U6.5
unnamed: U5.9, U6.9
unnamed: U5.10, U6.6
unnamed: U5.15, U6.2
OCTAVE_00: J6.2, U7.10
OCTAVE_01: J6.1, U7.9
SPEAKER: J1.2, J7.2, LS1.S, LS1.T, U7.13
VCC: C3.1, J2.1, J5.1, R2.1, U1.4, U1.11, U1.16, U2.4, U2.5, U2.8, U3.5, U3.16, U4.5, U4.16, U5.5, U5.16, U6.1, U6.20, U7.16

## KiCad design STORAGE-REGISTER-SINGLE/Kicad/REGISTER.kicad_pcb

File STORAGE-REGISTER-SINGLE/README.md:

# 8-bit Register

DESCRIPTION TODO

<br/>

## Schematic

Made with Kicad

[SCHEMATIC](https://github.com/theWickedWebDev/8-bit-computer/blob/master/STORAGE-REGISTER-SINGLE/schematic.pdf?raw=true)

<br/>

## PCB
Made with Kicad and fabricated with [JLCPCB](https://jlcpcb.com/)

Actual cost for me to fabricate this board.

| Fab 	    | S&H 	    | Total     |
|----	    |----	    |----       |
|  $9.50	|  $12.80 	|  $22.30   |

<br/>

<br/>

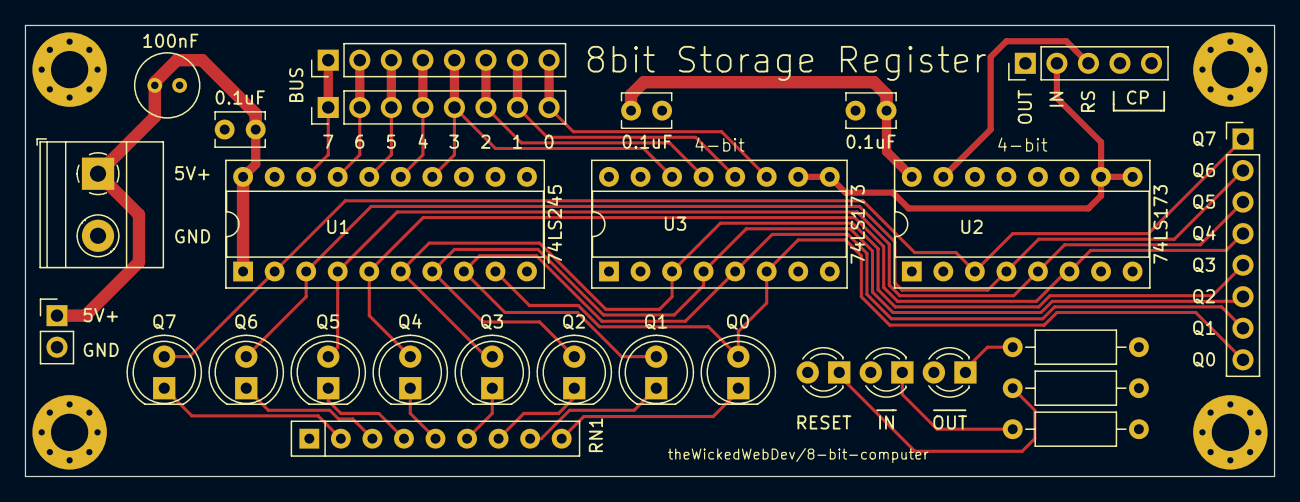
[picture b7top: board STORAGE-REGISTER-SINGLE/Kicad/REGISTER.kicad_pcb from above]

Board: 4 copper layers, 100.6 x 36.3 mm, 28 parts (0 on the bottom side), 33 nets.

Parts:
C1, C2, C3: CP1; C_Disc_D3.8mm_W2.6mm_P2.50mm
C4: CP1; C_Radial_D5.0mm_H7.0mm_P2.00mm
D1, D2, D3, D4, D5, D6, D7, D8: LED; LED_D5.0mm
D9, D10, D11: LED; LED_D3.0mm
J1: Screw_Terminal_01x02; TerminalBlock_Phoenix_MKDS-1,5-2_1x02_P5.00mm_Horizontal
J2, J5, J8: Conn_01x08; PinHeader_1x08_P2.54mm_Vertical
J3: Conn_01x02; PinHeader_1x02_P2.54mm_Vertical
J6: Conn_01x05; PinHeader_1x05_P2.54mm_Vertical
R1, R2, R3: R_Small_US; R_Axial_DIN0207_L6.3mm_D2.5mm_P10.16mm_Horizontal
RN1: R_Network08; R_Array_SIP9
U1: 74LS245; DIP-20_W7.62mm_Socket
U2, U3: 74LS173; DIP-16_W7.62mm_Socket

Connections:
BUS_00: J2.8, J5.8, U1.11, U3.11
BUS_01: J2.7, J5.7, U1.12, U3.12
BUS_02: J2.6, J5.6, U1.13, U3.13
BUS_03: J2.5, J5.5, U1.14, U3.14
BUS_04: J2.4, J5.4, U1.15, U2.11
BUS_05: J2.3, J5.3, U1.16, U2.12
BUS_06: J2.2, J5.2, U1.17, U2.13
BUS_07: J2.1, J5.1, U1.18, U2.14
CLOCK: J6.4, J6.5, U2.7, U3.7
GND: C1.2, C2.2, C3.2, C4.2, J1.2, J3.2, R1.2, R2.2, R3.2, RN1.1, U1.10, U2.1, U2.2, U2.8, U3.1, U3.2, U3.8
unnamed: D1.1, RN1.9
unnamed: D2.1, RN1.8
unnamed: D3.1, RN1.7
unnamed: D4.1, RN1.6
unnamed: D5.1, RN1.5
unnamed: D6.1, RN1.4
unnamed: D7.1, RN1.3
unnamed: D8.1, RN1.2
unnamed: D9.1, R1.1
unnamed: D10.1, R2.1
unnamed: D11.1, R3.1
Q0: D1.2, J8.8, U1.9, U3.6
Q1: D2.2, J8.7, U1.8, U3.5
Q2: D3.2, J8.6, U1.7, U3.4
Q3: D4.2, J8.5, U1.6, U3.3
Q4: D5.2, J8.4, U1.5, U2.6
Q5: D6.2, J8.3, U1.4, U2.5
Q6: D7.2, J8.2, U1.3, U2.4
Q7: D8.2, J8.1, U1.2, U2.3
REGISTER_IN: D10.2, J6.2, U2.9, U2.10, U3.9, U3.10
REGISTER_OUT: D11.2, J6.1, U1.19
RESET: D9.2, J6.3, U2.15, U3.15
VCC: C1.1, C2.1, C3.1, C4.1, J1.1, J3.1, U1.1, U1.20, U2.16, U3.16
